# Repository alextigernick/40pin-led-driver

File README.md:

A 40 output led driver shift register board. Intended to be used to drive a large 5 section 7-segment led clock.

[BOM is here](./BOM.xls)

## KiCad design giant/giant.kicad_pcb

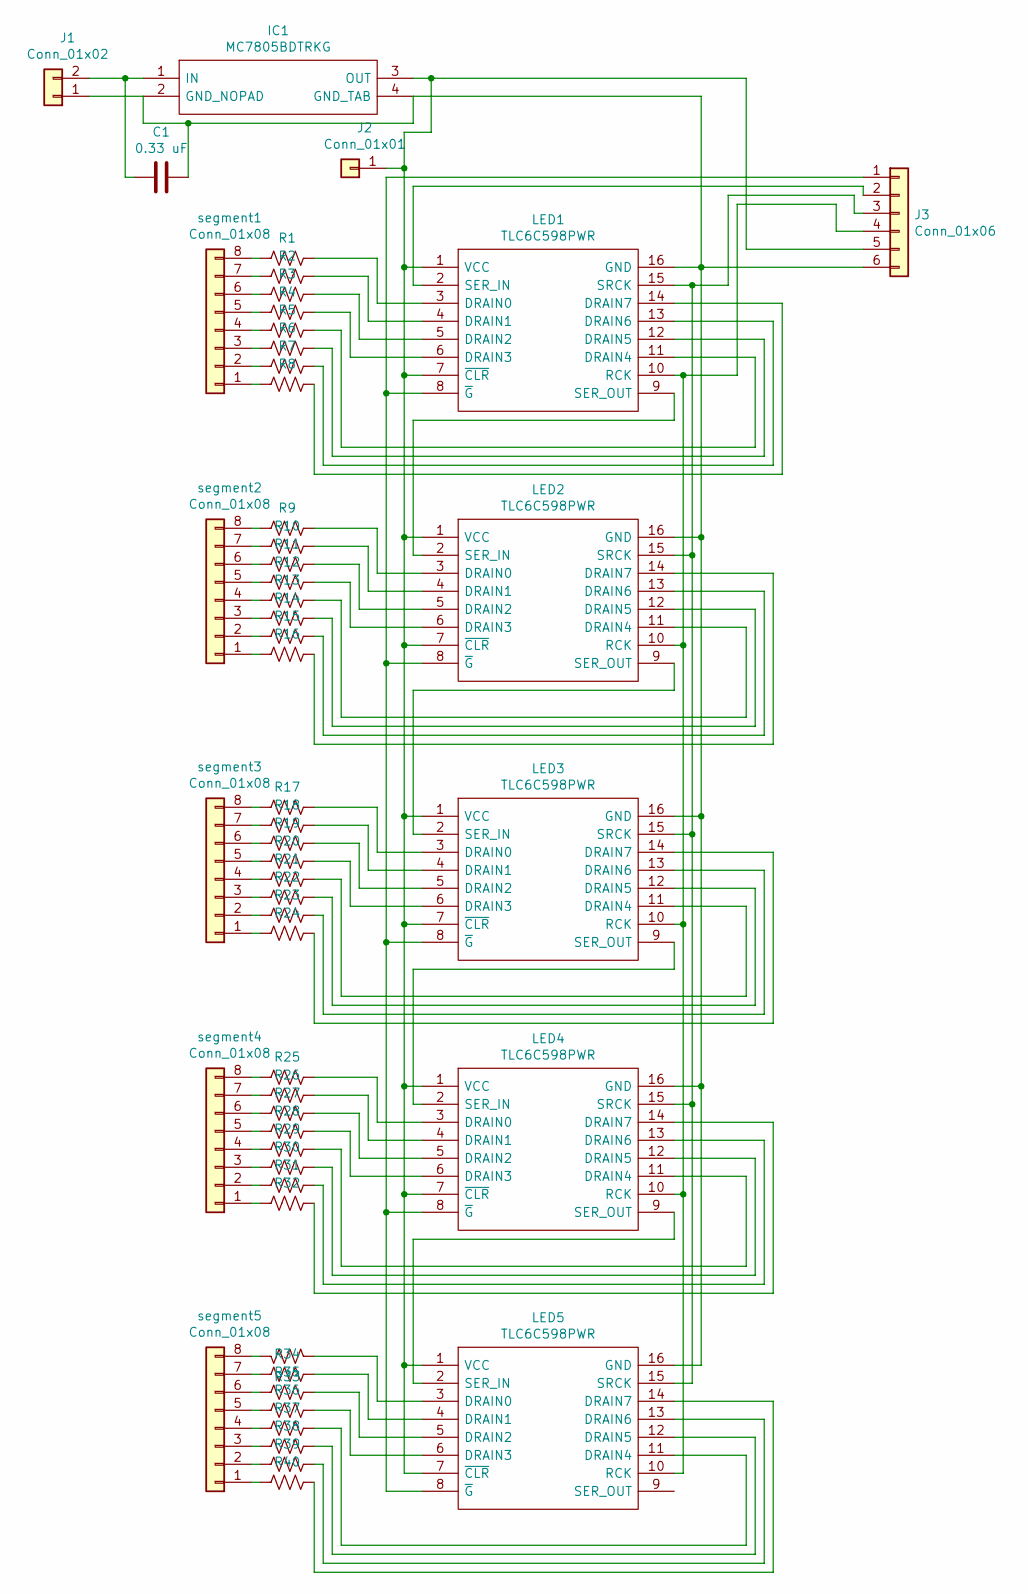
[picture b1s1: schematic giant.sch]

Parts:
C1: 0.33 uF; C_0603_1608Metric_Pad1.05x0.95mm_HandSolder; PartNumber 885012206049
IC1: MC7805BDTRKG; TO229P990X238-4N; Manufacturer_Part_Number MC7805BDTRKG; Mouser Part Number 863-MC7805BDTRKG
J1: Conn_01x02; PinHeader_1x02_P2.54mm_Vertical
J2: Conn_01x01; PinHeader_1x01_P2.54mm_Vertical
J3: Conn_01x06; PinHeader_1x06_P2.54mm_Vertical
LED1, LED2, LED3, LED4, LED5: TLC6C598PWR; SOP65P640X120-16N; Manufacturer_Part_Number TLC6C598PWR; Mouser Part Number 595-TLC6C598PWR
R1, R2, R3, R4, R5, R6, R7, R8, R9, R10, R11, R12, R13, R14, R15, R16, R17, R18, R19, R20, R21, R22, R23, R24, R25, R26, R27, R28, R29, R30, R31, R32, R33, R34, R35, R36, R37, R38, R39, R40: R_US; R_0805_2012Metric_Pad1.15x1.40mm_HandSolder; PartNumber ESR10EZPJ201
segment1, segment2, segment3, segment4, segment5: Conn_01x08; PinHeader_1x08_P2.54mm_Vertical

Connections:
unnamed: C1.1, IC1.2 (GND_NOPAD), IC1.4 (GND_TAB), J1.1, J3.6, LED1.16 (GND), LED2.16 (GND), LED3.16 (GND), LED4.16 (GND), LED5.16 (GND)
unnamed: C1.2, IC1.1 (IN), J1.2
unnamed: IC1.3 (OUT), J2.1, J3.5, LED1.1 (VCC), LED1.7 (~CLR), LED2.1 (VCC), LED2.7 (~CLR), LED3.1 (VCC), LED3.7 (~CLR), LED4.1 (VCC), LED4.7 (~CLR), LED5.1 (VCC), LED5.7 (~CLR)
unnamed: J3.1, LED1.8 (~G), LED2.8 (~G), LED3.8 (~G), LED4.8 (~G), LED5.8 (~G)
unnamed: J3.2, LED1.2 (SER_IN)
unnamed: J3.3, LED1.15 (SRCK), LED2.15 (SRCK), LED3.15 (SRCK), LED4.15 (SRCK), LED5.15 (SRCK)
unnamed: J3.4, LED1.10 (RCK), LED2.10 (RCK), LED3.10 (RCK), LED4.10 (RCK), LED5.10 (RCK)
unnamed: LED1.3 (DRAIN0), R1.2
unnamed: LED1.4 (DRAIN1), R2.2
unnamed: LED1.5 (DRAIN2), R3.2
unnamed: LED1.6 (DRAIN3), R4.2
unnamed: LED1.9 (SER_OUT), LED2.2 (SER_IN)
unnamed: LED1.11 (DRAIN4), R5.2
unnamed: LED1.12 (DRAIN5), R6.2
unnamed: LED1.13 (DRAIN6), R7.2
unnamed: LED1.14 (DRAIN7), R8.2
unnamed: LED2.3 (DRAIN0), R9.2
unnamed: LED2.4 (DRAIN1), R10.2
unnamed: LED2.5 (DRAIN2), R11.2
unnamed: LED2.6 (DRAIN3), R12.2
unnamed: LED2.9 (SER_OUT), LED3.2 (SER_IN)
unnamed: LED2.11 (DRAIN4), R13.2
unnamed: LED2.12 (DRAIN5), R14.2
unnamed: LED2.13 (DRAIN6), R15.2
unnamed: LED2.14 (DRAIN7), R16.2
unnamed: LED3.3 (DRAIN0), R17.2
unnamed: LED3.4 (DRAIN1), R18.2
unnamed: LED3.5 (DRAIN2), R19.2
unnamed: LED3.6 (DRAIN3), R20.2
unnamed: LED3.9 (SER_OUT), LED4.2 (SER_IN)
unnamed: LED3.11 (DRAIN4), R21.2
unnamed: LED3.12 (DRAIN5), R22.2
unnamed: LED3.13 (DRAIN6), R23.2
unnamed: LED3.14 (DRAIN7), R24.2
unnamed: LED4.3 (DRAIN0), R25.2
unnamed: LED4.4 (DRAIN1), R26.2
unnamed: LED4.5 (DRAIN2), R27.2
unnamed: LED4.6 (DRAIN3), R28.2
unnamed: LED4.9 (SER_OUT), LED5.2 (SER_IN)
unnamed: LED4.11 (DRAIN4), R29.2
unnamed: LED4.12 (DRAIN5), R30.2
unnamed: LED4.13 (DRAIN6), R31.2
unnamed: LED4.14 (DRAIN7), R32.2
unnamed: LED5.3 (DRAIN0), R33.2
unnamed: LED5.4 (DRAIN1), R34.2
unnamed: LED5.5 (DRAIN2), R35.2
unnamed: LED5.6 (DRAIN3), R36.2
unnamed: LED5.11 (DRAIN4), R37.2
unnamed: LED5.12 (DRAIN5), R38.2
unnamed: LED5.13 (DRAIN6), R39.2
unnamed: LED5.14 (DRAIN7), R40.2
unnamed: R1.1, segment1.8
unnamed: R2.1, segment1.7
unnamed: R3.1, segment1.6
unnamed: R4.1, segment1.5
unnamed: R5.1, segment1.4
unnamed: R6.1, segment1.3
unnamed: R7.1, segment1.2
unnamed: R8.1, segment1.1
unnamed: R9.1, segment2.8
unnamed: R10.1, segment2.7
unnamed: R11.1, segment2.6
unnamed: R12.1, segment2.5
unnamed: R13.1, segment2.4
unnamed: R14.1, segment2.3
unnamed: R15.1, segment2.2
unnamed: R16.1, segment2.1
unnamed: R17.1, segment3.8
unnamed: R18.1, segment3.7
unnamed: R19.1, segment3.6
unnamed: R20.1, segment3.5
unnamed: R21.1, segment3.4
unnamed: R22.1, segment3.3
unnamed: R23.1, segment3.2
unnamed: R24.1, segment3.1
unnamed: R25.1, segment4.8
unnamed: R26.1, segment4.7
unnamed: R27.1, segment4.6
unnamed: R28.1, segment4.5
unnamed: R29.1, segment4.4
unnamed: R30.1, segment4.3
unnamed: R31.1, segment4.2
unnamed: R32.1, segment4.1
unnamed: R33.1, segment5.8
unnamed: R34.1, segment5.7
unnamed: R35.1, segment5.6
unnamed: R36.1, segment5.5
unnamed: R37.1, segment5.4
unnamed: R38.1, segment5.3
unnamed: R39.1, segment5.2
unnamed: R40.1, segment5.1

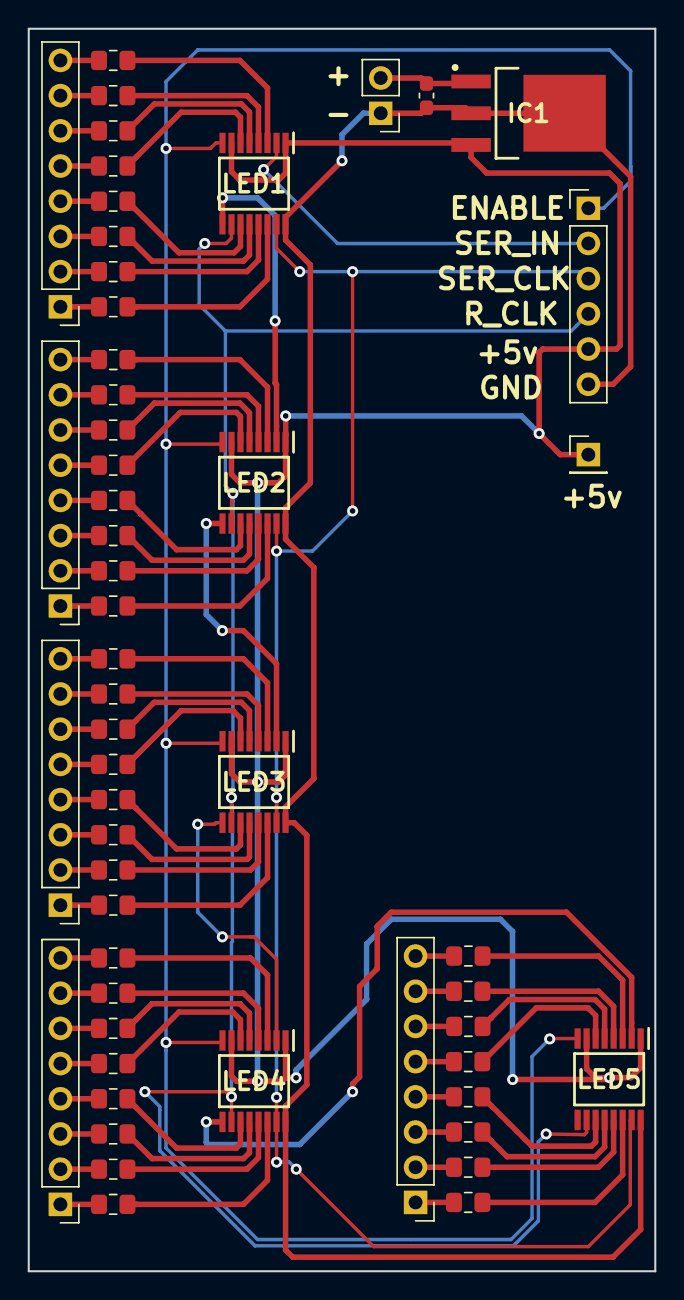
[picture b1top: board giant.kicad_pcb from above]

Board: 2 copper layers, 45.2 x 89.7 mm, 55 parts (0 on the bottom side), 91 nets.

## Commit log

2019-01-09 Initial
2019-01-09 Improved schematic layout for both cleanliness and programming ease
2019-01-09 Added text and updated 3d view
2019-01-09 added gerber files and basic README
